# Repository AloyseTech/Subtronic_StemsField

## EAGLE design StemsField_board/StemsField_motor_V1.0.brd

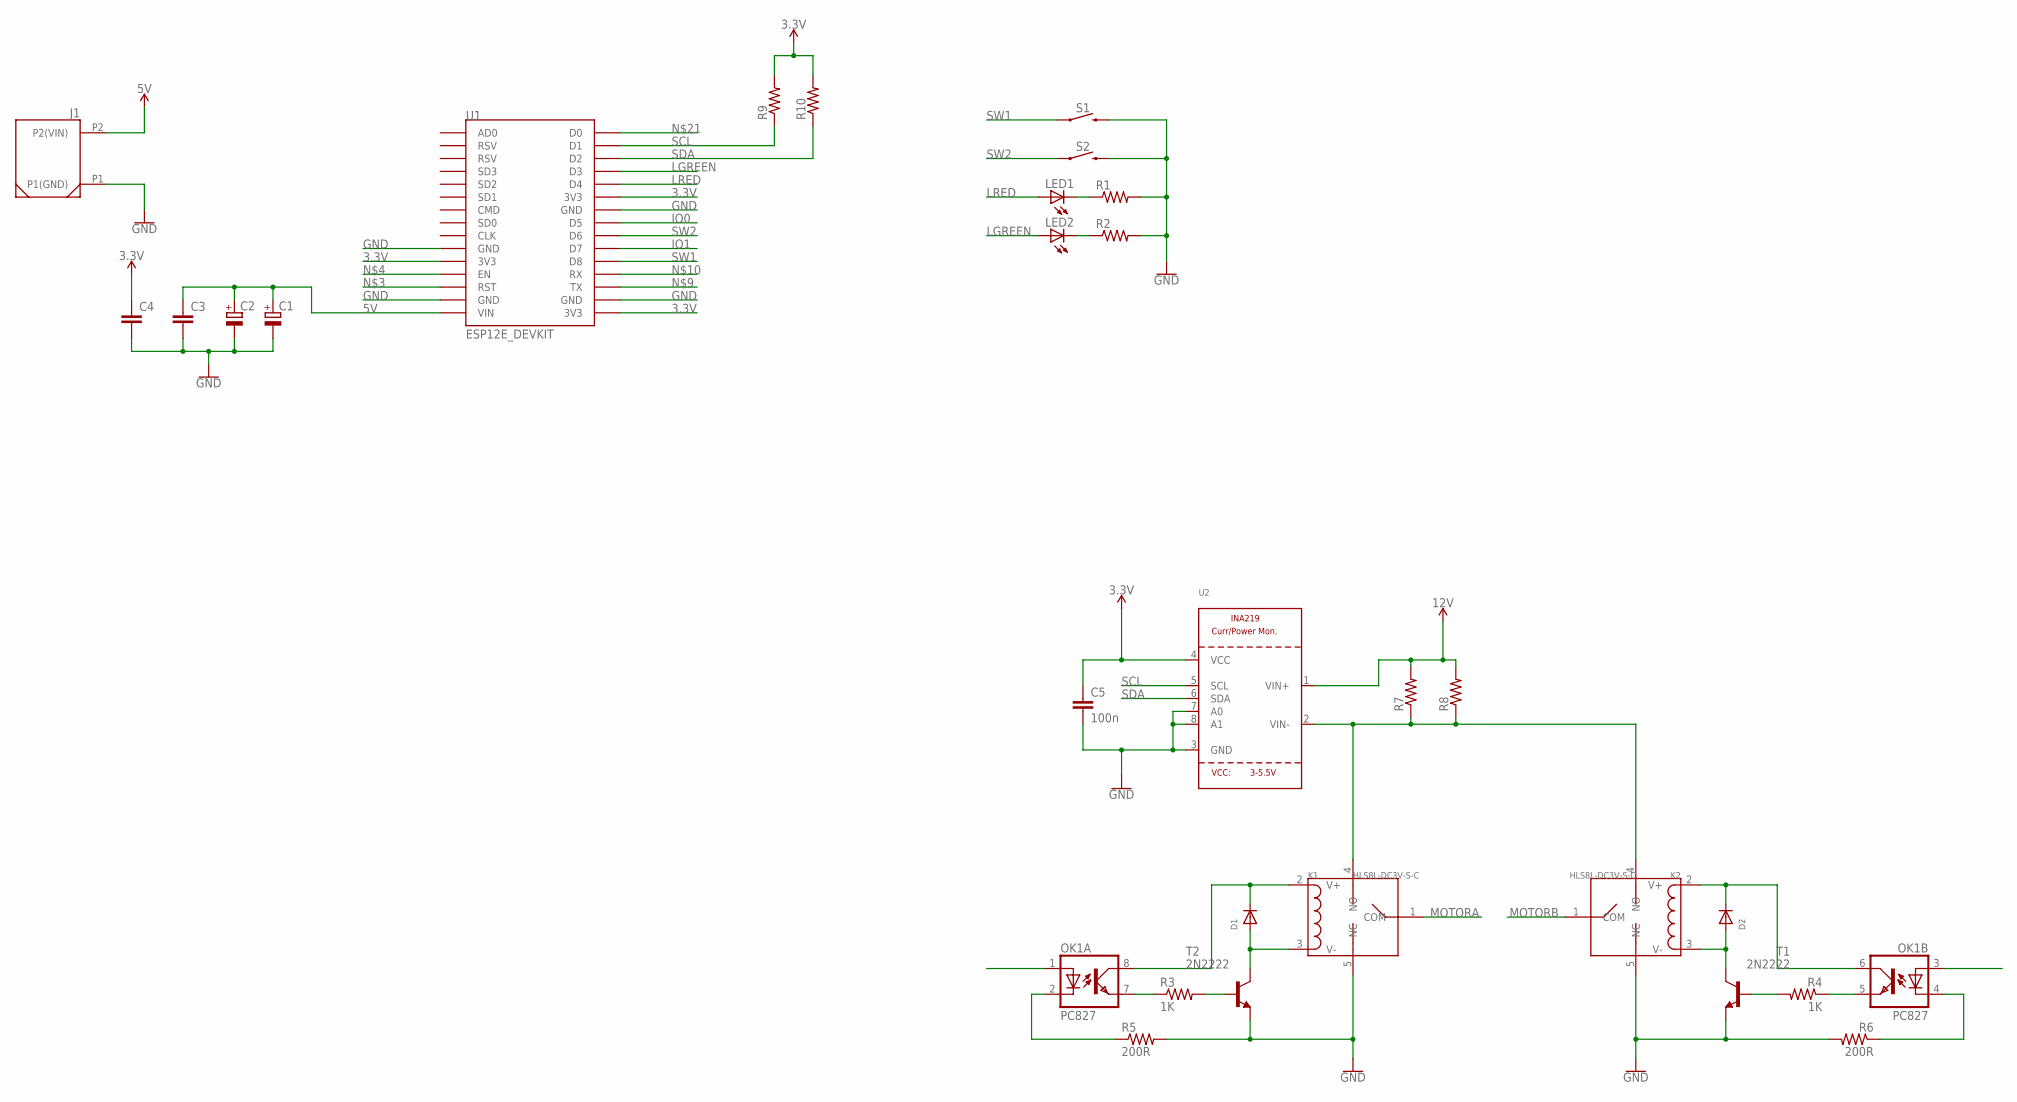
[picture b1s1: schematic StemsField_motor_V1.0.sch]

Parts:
C1, C2: CPOL-EUE3.5-8; E3,5-8
C3, C4: C-EU025-024X044; C025-024X044
C5: 100n; C025-024X044
D1, D2: DIODEDO-1N4148; DO-1N4148
J1: XT30PWM; XT30PW-M
K1, K2: HLS8L-DC3V-S-C; REY5-19.0X15.0X15.0MM
LED1, LED2: LED3MM
OK1: PC827; DIL08
R1, R2, R9, R10: R-US_0204/5; 0204/5
R3, R4: 1K; 0204/7
R5, R6: 200R; 0204/7
R7: R-US_0204/7; 0204/7
R8: R-US_R2512; R2512
S1, S2: MOMENTARY-SWITCH-SPST-PTH-6.0MM; TACTILE_SWITCH_PTH_6.0MM
T1, T2: 2N2222; TO92-EBC-OVAL
U1: ESP12E_DEVKIT
U2: INA219; SOT23-8

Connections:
3.3V: C4.1, C5.1, R9.2, R10.2, U1.3V3@0 (3V3), U1.3V3@1 (3V3), U1.3V3@2 (3V3), U2.4 (VCC)
5V: C1.+, C2.+, C3.1, J1.P2 (P2(VIN)), U1.VIN
12V: R7.2, R8.2, U2.1 (VIN+)
GND: C1.-, C2.-, C3.2, C4.2, C5.2, J1.P1 (P1(GND)), K1.5 (NC), K2.5 (NC), R1.2, R2.2, R5.2, R6.2, S1.3 (2), S2.3 (2), T1.E, T2.E, U1.GND@0 (GND), U1.GND@1 (GND), U1.GND@2 (GND), U1.GND@3 (GND), U2.3 (GND), U2.7 (A0), U2.8 (A1)
IO0: U1.D5
IO1: U1.D7
LGREEN: LED2.A, U1.D3
LRED: LED1.A, U1.D4
MOTORA: K1.1 (COM)
MOTORB: K2.1 (COM)
unnamed: LED1.K (C), R1.1
unnamed: LED2.K (C), R2.1
unnamed: D2.C, K2.2 (V+), OK1.6 (COL)
unnamed: D2.A, K2.3 (V-), T1.C
unnamed: K1.4 (NO), K2.4 (NO), R7.1, R8.1, U2.2 (VIN-)
unnamed: R3.2, T2.B
unnamed: OK1.7 (EMIT), R3.1
unnamed: D1.C, K1.2 (V+), OK1.8 (COL)
unnamed: D1.A, K1.3 (V-), T2.C
unnamed: OK1.2 (C), R5.1
unnamed: OK1.5 (EMIT), R4.1
unnamed: R4.2, T1.B
unnamed: OK1.4 (C), R6.1
SCL: R9.1, U1.D1, U2.5 (SCL)
SDA: R10.1, U1.D2, U2.6 (SDA)
SW1: S1.1, U1.D8
SW2: S2.1, U1.D6

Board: 2 copper layers, 29 parts (0 on the bottom side), 23 nets, no tracks yet.

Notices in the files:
parts and their libraries:
SparkFun-Switches: Licensing: Creative Commons ShareAlike 4.0 International - https://creativecommons.org/licenses/by-sa/4.0
microbuilder: This work is placed in the public domain, and may be freely used for commercial and non-commercial work with the following conditions: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
